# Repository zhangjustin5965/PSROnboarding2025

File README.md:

# PSROnboarding2025
# Justin Onboarding stuff

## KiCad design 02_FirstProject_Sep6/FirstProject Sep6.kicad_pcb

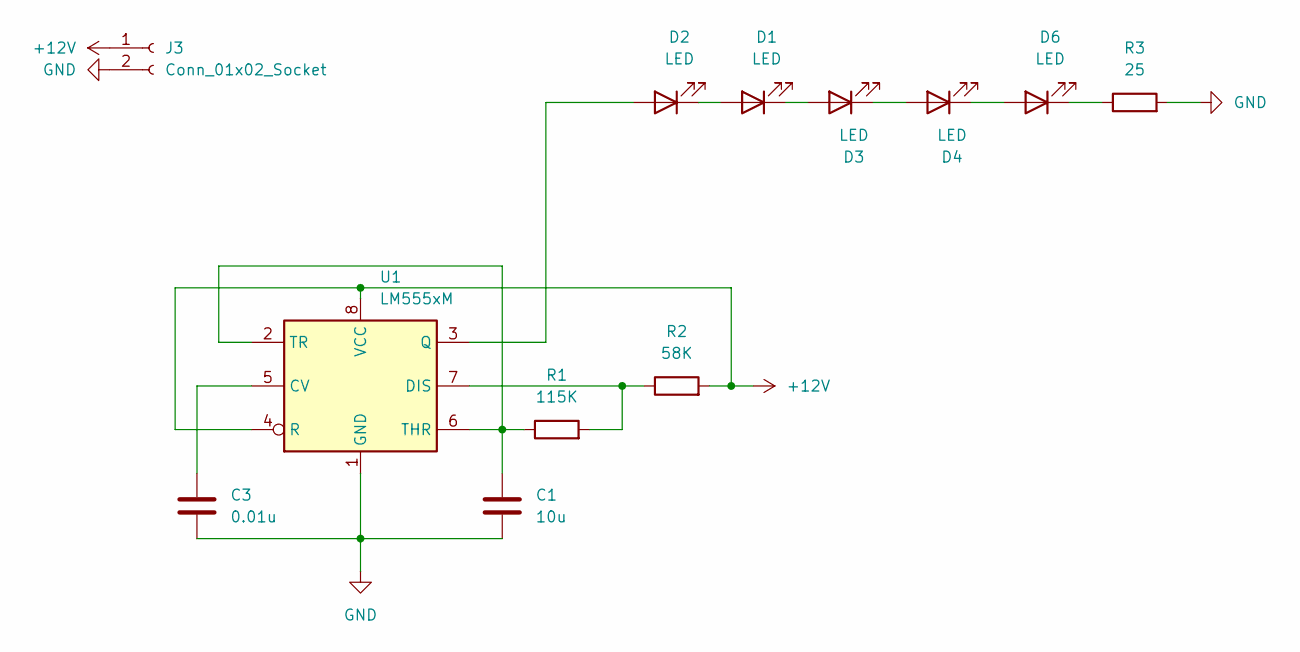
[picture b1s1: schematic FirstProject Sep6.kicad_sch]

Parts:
C1: 10u; C_0805_2012Metric
C3: 0.01u; C_0805_2012Metric
D1, D2, D3, D4, D6: LED; HSMA-A421-Y00M1
J3: Conn_01x02_Socket; Molex_Micro-Fit_3.0_43650-0200_1x02_P3.00mm_Horizontal
R1: 115K; R_0805_2012Metric
R2: 58K; R_0805_2012Metric
R3: 25; R_0805_2012Metric
U1: LM555xM; SOIC-8_3.9x4.9mm_P1.27mm

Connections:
+12V: J3.1, R2.2, U1.4 (R), U1.8 (VCC)
GND: C1.2, C3.2, J3.2, R3.2, U1.1 (GND)
unnamed: D1.2 (A), D2.1 (K)
unnamed: D1.1 (K), D3.2 (A)
unnamed: D2.2 (A), U1.3 (Q)
unnamed: D3.1 (K), D4.2 (A)
unnamed: D4.1 (K), D6.2 (A)
unnamed: D6.1 (K), R3.1
unnamed: C3.1, U1.5 (CV)
unnamed: R1.2, R2.1, U1.7 (DIS)
unnamed: C1.1, R1.1, U1.2 (TR), U1.6 (THR)

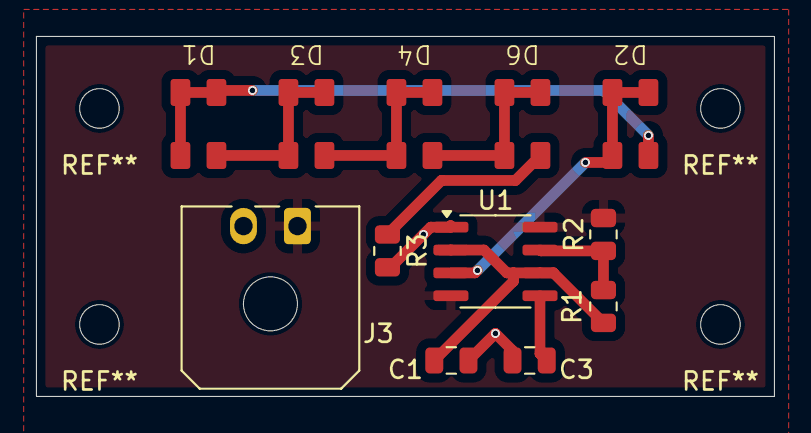
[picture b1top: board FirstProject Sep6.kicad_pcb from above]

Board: 2 copper layers, 41.0 x 20.0 mm, 12 parts (0 on the bottom side), 11 nets.

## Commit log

2025-09-06 test
2025-09-06 Default
2025-09-06 Test2
2025-09-06 Test3
